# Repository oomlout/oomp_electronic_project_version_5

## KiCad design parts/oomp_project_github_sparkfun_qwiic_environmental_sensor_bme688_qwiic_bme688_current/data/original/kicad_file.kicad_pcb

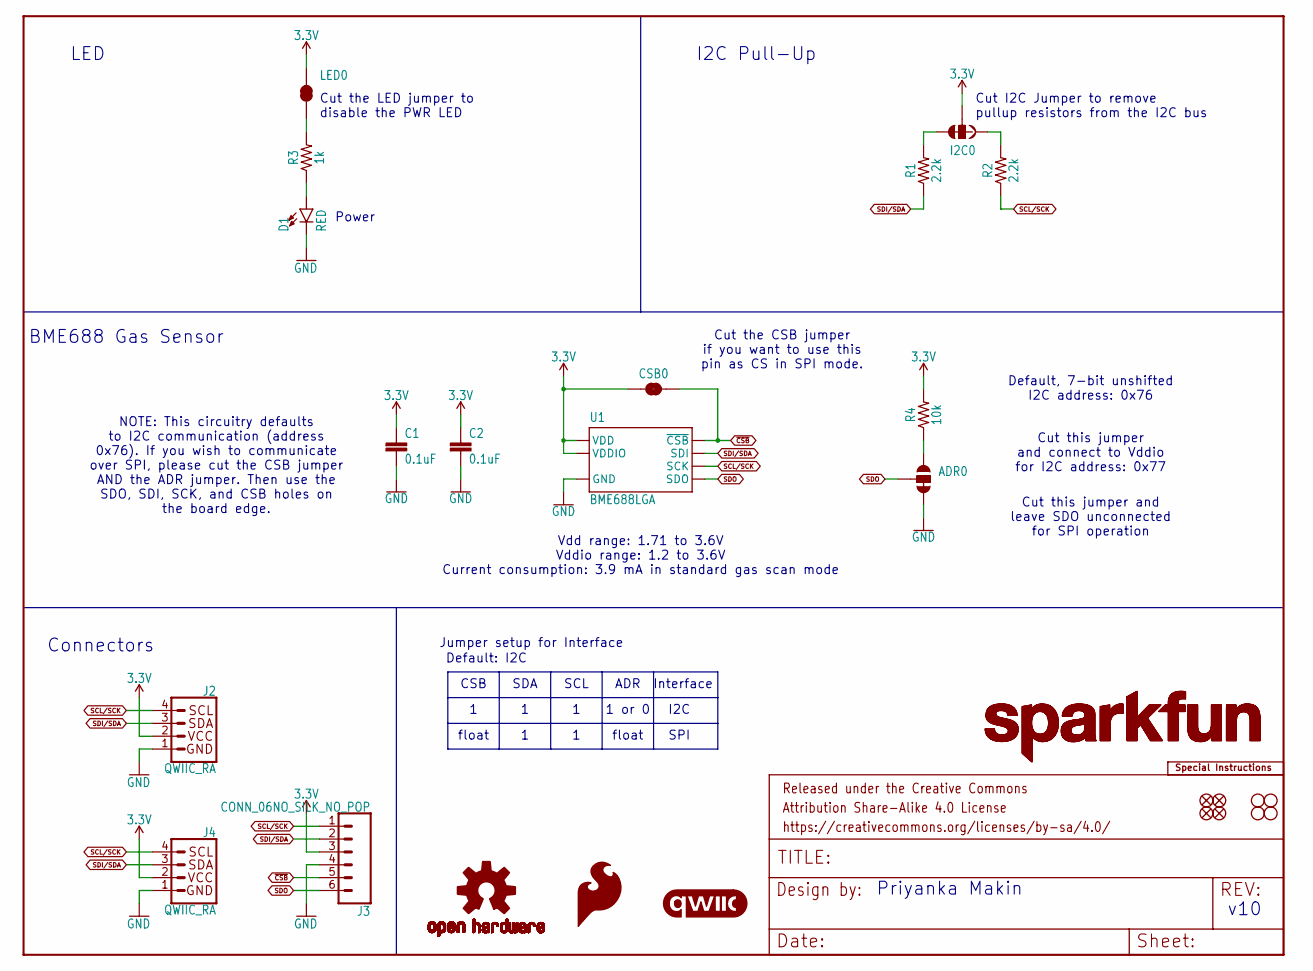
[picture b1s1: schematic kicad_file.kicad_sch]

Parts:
ADR0: JUMPER-SMT_3_1-NC_TRACE_SILK; SMT-JUMPER_3_1-NC_TRACE_SILK
C1, C2: 0.1uF; 0603
CSB0: JUMPER-SMT_2_NC_TRACE_SILK; SMT-JUMPER_2_NC_TRACE_SILK
D1: RED; LED-0603
FRAME1: FRAME-LETTER; CREATIVE_COMMONS
I2C0: JUMPER-SMT_3_2-NC_TRACE_SILK; SMT-JUMPER_3_2-NC_TRACE_SILK
J2, J4: QWIIC_RA; JST04_1MM_RA
J3: CONN_06NO_SILK_NO_POP; 1X06_NO_SILK
JP1, JP2, JP5, JP6: FIDUCIALUFIDUCIAL; FIDUCIAL-MICRO
JP3, JP4, JP7, JP8: STAND-OFF
LED0: JUMPER-SMT_2_NC_TRACE_SILK; SMT-JUMPER_2_NC_TRACE_SILK
LOGO1: SPECIAL_INSTRUCTIONS-ORDERING; ORDERING_INSTRUCTIONS
LOGO2: QWIIC_LOGO_5MM; QWIIC_5MM
LOGO3, LOGO6: SFE_LOGO_NAME.1_INCH; SFE_LOGO_NAME_.1
LOGO4: SFE_LOGO_FLAME.1_INCH; SFE_LOGO_FLAME_.1
LOGO5: OSHW-LOGOS; OSHW-LOGO-S
R1, R2: 2.2k; 0603
R3: 1k; 0603
R4: 10k; 0603
U1: BME688LGA; LGA_8PIN

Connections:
3.3V: C1.1, C2.1, CSB0.1, I2C0.2, J2.2, J3.3, J4.2, LED0.2, R4.2, U1.6 (VDDIO), U1.8 (VDD)
GND: ADR0.3, C1.2, C2.2, D1.C, J2.1, J3.4, J4.1, U1.1 (GND), U1.7 (GND)
unnamed: LED0.1, R3.2
unnamed: I2C0.3, R1.2
unnamed: D1.A, R3.1
unnamed: I2C0.1, R2.2
unnamed: ADR0.1, R4.1
SCL/SCK: J2.4, J3.1, J4.4, R2.1, U1.4 (SCK)
SDI/SDA: J2.3, J3.2, J4.3, R1.1, U1.3 (SDI)
SDO: ADR0.2, J3.6, U1.5 (SDO)
~CSB: CSB0.2, J3.5, U1.2 (~CSB)

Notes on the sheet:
Priyanka Makin
Cut the LED jumper to disable the PWR LED
Cut this jumper and connect to Vddio for I2C address: 0x77
float
LED
v10
1 or 0
NOTE: This circuitry defaults to I2C communication (address 0x76). If you wish to communicate over SPI, please cut the CSB jumper AND the ADR jumper. Then use the SDO, SDI, SCK, and CSB holes on the board edge.
Cut I2C Jumper to remove pullup resistors from the I2C bus
Default: I2C
BME688 Gas Sensor
I2C
Jumper setup for Interface
Interface
Connectors
Cut this jumper and leave SDO unconnected for SPI operation~{}
SCL
ADR
Power
SPI
SDA
Vdd range: 1.71 to 3.6V Vddio range: 1.2 to 3.6V Current consumption: 3.9 mA in standard gas scan mode
I2C Pull-Up
Default, 7-bit unshifted I2C address: 0x76
Cut the CSB jumper if you want to use this pin as CS in SPI mode.
CSB

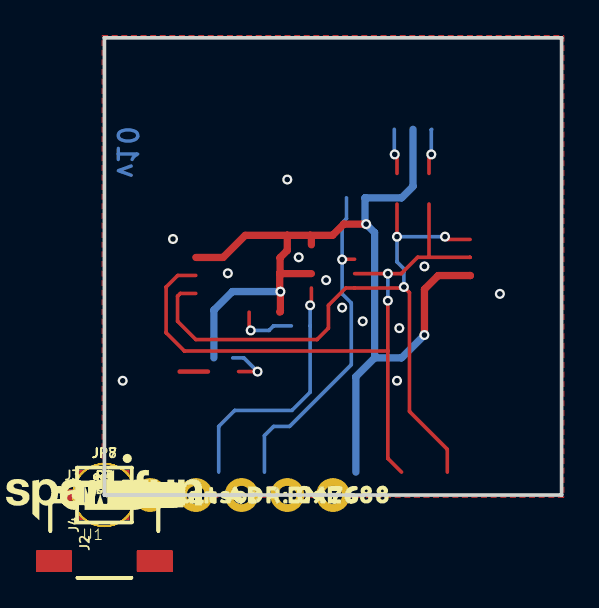
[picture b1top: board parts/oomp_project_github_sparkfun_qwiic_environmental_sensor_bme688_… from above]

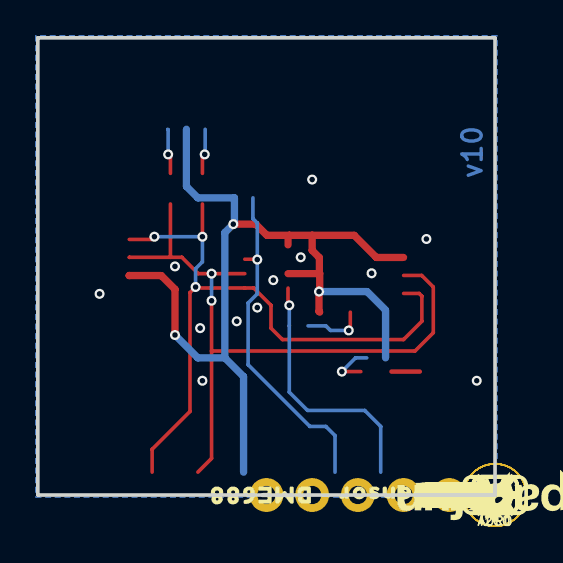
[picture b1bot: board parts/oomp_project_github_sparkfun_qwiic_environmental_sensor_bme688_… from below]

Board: 2 copper layers, 25.4 x 25.4 mm, 52 parts (22 on the bottom side), 11 nets.

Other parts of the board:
U$1, U$33: #GND#0
U$2, U$16: #SDO#0
U$3: #CSB#0
U$5: PWR0
U$6: #I2C#0
U$7, U$10: GAS_SENSOR_#_BME6880
U$8: #LED#0
U$9: 0X760
U$11: #ADR#0
U$12: DEFAULT_ADR#_0X760
U$13: 0X770
U$14, U$15: #3V3#0
U$19: #SDI#0
U$20: #SCK#0
U$21, U$22: ##CSB##0
U$35: #SDA#0
U$36: #SCL#0

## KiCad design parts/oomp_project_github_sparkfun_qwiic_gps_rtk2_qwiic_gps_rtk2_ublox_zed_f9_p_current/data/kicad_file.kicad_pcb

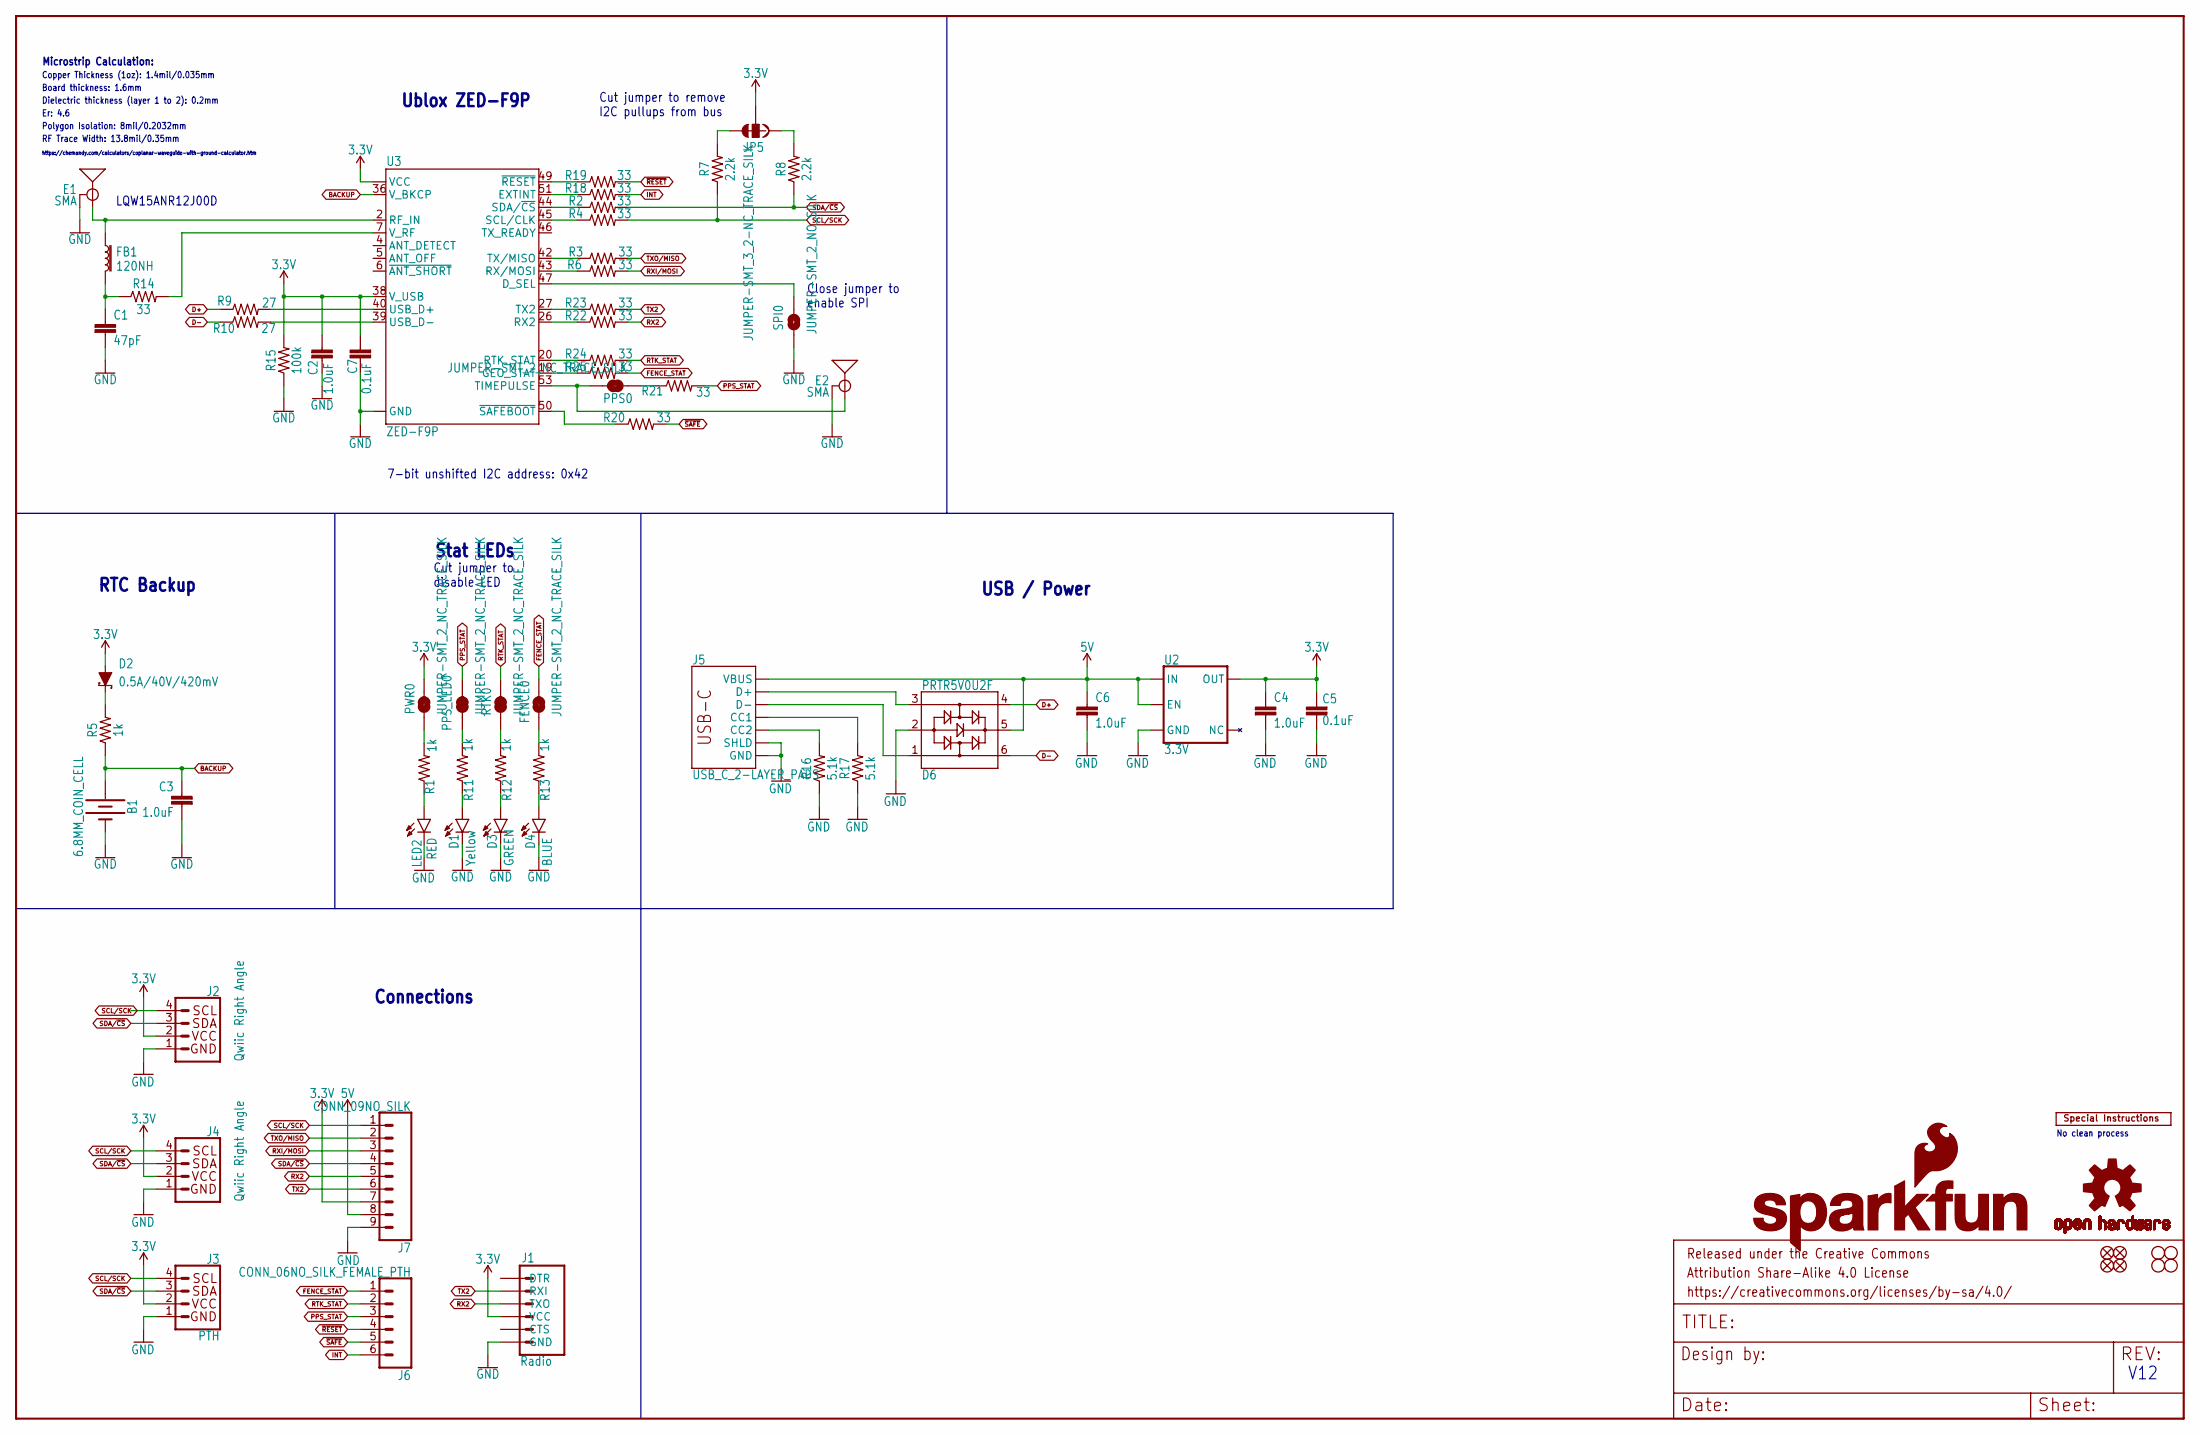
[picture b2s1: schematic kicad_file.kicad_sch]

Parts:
B1: 6.8MM_COIN_CELL; ML414H_IV01E
C1: 47pF; 0402
C2, C3, C4, C6: 1.0uF; 0603
C5, C7: 0.1uF; 0603
D1: Yellow; LED-0603
D2: 0.5A/40V/420mV; SOD-323
D3: GREEN; LED-0603
D4: BLUE; LED-0603
D6: PRTR5V0U2F; SOT886
E1, E2: SMA; SMA-EDGE
FB1: 120NH; 0402_MURATA
FENCE0: JUMPER-SMT_2_NC_TRACE_SILK; SMT-JUMPER_2_NC_TRACE_SILK
FRAME2: FRAME-LEDGER; CREATIVE_COMMONS
J1: Radio; 1X06_NO_SILK
J2, J4: Qwiic Right Angle; JST04_1MM_RA
J3: PTH; 1X04_NO_SILK
J5: USB_C_2-LAYER_PADS; USB-C-16P-2LAYER-PADS
J6: CONN_06NO_SILK_FEMALE_PTH; 1X06_NO_SILK
J7: CONN_09NO_SILK; 1X09_NO_SILK
JP5: JUMPER-SMT_3_2-NC_TRACE_SILK; SMT-JUMPER_3_2-NC_TRACE_SILK
JP21, JP61, JP71, JP81: FIDUCIALUFIDUCIAL; MICRO-FIDUCIAL
JP31, JP41, JP91, JP101: STAND-OFF
LED2: RED; LED-0603
LOGO1: OSHW-LOGOMINI; OSHW-LOGO-MINI
LOGO2: SFE_LOGO_NAME_FLAME.1_INCH; SFE_LOGO_NAME_FLAME_.1
PPS0: JUMPER-SMT_2_NC_TRACE_SILK; SMT-JUMPER_2_NC_TRACE_SILK
PPS_LED0: JUMPER-SMT_2_NC_TRACE_SILK; SMT-JUMPER_2_NC_TRACE_SILK
PWR0: JUMPER-SMT_2_NC_TRACE_SILK; SMT-JUMPER_2_NC_TRACE_SILK
R1, R5, R11, R12, R13: 1k; 0603
R2, R3, R4, R6, R14, R18, R19, R20, R21, R22, R23, R24, R25: 33; 0603
R7, R8: 2.2k; 0603
R9, R10: 27; 0603
R15: 100k; 0603
R16, R17: 5.1k; 0603
RTK0: JUMPER-SMT_2_NC_TRACE_SILK; SMT-JUMPER_2_NC_TRACE_SILK
SPI0: JUMPER-SMT_2_NO_SILK; SMT-JUMPER_2_NO_SILK
U2: 3.3V; SOT23-5
U3: ZED-F9P
U$2: SPECIAL_INSTRUCTIONS-ORDERING; ORDERING_INSTRUCTIONS

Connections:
3.3V: C2.1, C4.1, C5.2, C7.2, D2.A, J1.4 (VCC), J2.2, J3.2 (VCC), J4.2, J7.7, JP5.2, PWR0.2, R15.2, U2.5 (OUT), U3.33 (VCC), U3.34 (VCC), U3.38 (V_USB)
5V: C6.1, D6.5, J5.VBUS1 (VBUS), J5.VBUS2 (VBUS), J7.8, U2.1 (IN), U2.3 (EN)
ANT_VCC: C1.1, FB1.P2 (2), R14.1
BACKUP: B1.+, C3.1, R5.1, U3.36 (V_BKCP)
CC1: J5.A5 (CC1), R17.2
CC2: J5.B5 (CC2), R16.2
D+: D6.4, R9.1
D-: D6.6, R10.1
D_SEL: SPI0.2, U3.47 (D_SEL)
FENCE_STAT: FENCE0.2, J6.1, R25.2
GND: B1.-, C1.2, C2.2, C3.2, C4.2, C5.1, C6.2, C7.1, D1.C, D3.C, D4.C, D6.2, E1.GND@0 (GND), E1.GND@1 (GND), E1.GND@2 (GND), E1.GND@3 (GND), E2.GND@0 (GND), E2.GND@1 (GND), E2.GND@2 (GND), E2.GND@3 (GND), J1.6 (GND), J2.1, J3.1 (GND), J4.1, J5.GND, J5.GND2 (GND), J5.SHLD1 (SHLD), J5.SHLD2 (SHLD), J5.SHLD3 (SHLD), J5.SHLD4 (SHLD), J7.9, LED2.C, R15.1, R16.1, R17.1, SPI0.1, U2.2 (GND), U3.1 (GND), U3.3 (GND), U3.12 (GND), U3.14 (GND), U3.32 (GND), U3.37 (GND), U3.41 (GND), U3.48 (GND), U3.55 (GND), U3.56 (GND), U3.57 (GND), U3.58 (GND), U3.59 (GND), U3.60 (GND), U3.61 (GND), U3.62 (GND), U3.63 (GND), U3.64 (GND), U3.65 (GND), U3.66 (GND), U3.67 (GND), U3.68 (GND), U3.69 (GND), U3.70 (GND), U3.71 (GND), U3.72 (GND), U3.73 (GND), U3.74 (GND), U3.75 (GND), U3.76 (GND), U3.77 (GND), U3.78 (GND), U3.79 (GND), U3.80 (GND), U3.81 (GND), U3.82 (GND), U3.83 (GND), U3.84 (GND), U3.85 (GND), U3.86 (GND), U3.87 (GND), U3.88 (GND), U3.89 (GND), U3.90 (GND), U3.91 (GND), U3.92 (GND), U3.93 (GND), U3.94 (GND), U3.95 (GND), U3.96 (GND), U3.97 (GND), U3.98 (GND), U3.99 (GND), U3.100 (GND), U3.101 (GND), U3.102 (GND)
GPS_ANT1: E1.SIG (SIGNAL), FB1.P1 (1), U3.2 (RF_IN)
INT: J6.6, R18.2
unnamed: D3.A, R12.1
unnamed: D1.A, R11.1
unnamed: R12.2, RTK0.1
unnamed: PPS_LED0.1, R11.2
unnamed: JP5.1, R8.2
unnamed: D2.C, R5.2
unnamed: D4.A, R13.1
unnamed: JP5.3, R7.2
unnamed: FENCE0.1, R13.2
unnamed: LED2.A, R1.1
unnamed: R9.2, U3.40 (USB_D+)
unnamed: R10.2, U3.39 (USB_D-)
unnamed: R14.2, U3.7 (V_RF)
unnamed: R22.1, U3.26 (RX2)
unnamed: R18.1, U3.51 (EXTINT)
unnamed: R19.1, U3.49 (~RESET)
unnamed: PWR0.1, R1.2
unnamed: R20.1, U3.50 (~SAFEBOOT)
unnamed: R24.1, U3.20 (RTK_STAT)
unnamed: R25.1, U3.19 (GEO_STAT)
unnamed: PPS0.1, R21.1
PPS: E2.SIG (SIGNAL), PPS0.2, U3.53 (TIMEPULSE)
PPS_STAT: J6.3, PPS_LED0.2, R21.2
RTK_STAT: J6.2, R24.2, RTK0.2
RX2: J1.3 (TXO), J7.5, R22.2
RXI/MOSI: J7.3, R6.2
RXLV: R6.1, U3.43 (RX/MOSI)
SCL/SCK: J2.4, J3.4 (SCL), J4.4, J7.1, R4.2, R7.1
SCL_LV: R4.1, U3.45 (SCL/CLK)
SDA/~CS: J2.3, J3.3 (SDA), J4.3, J7.4, R2.2, R8.1
SDA_LV: R2.1, U3.44 (SDA/~CS)
TX2: J1.2 (RXI), J7.6, R23.2
TX2_P: R23.1, U3.27 (TX2)
TXLV: R3.1, U3.42 (TX/MISO)
TXO/MISO: J7.2, R3.2
UNP_D+: D6.3, J5.A6 (D+), J5.B6 (D+)
UNP_D-: D6.1, J5.A7 (D-), J5.B7 (D-)
~RESET: J6.4, R19.2
~SAFE: J6.5, R20.2

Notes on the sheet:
V12
RTC Backup
Dielectric thickness (layer 1 to 2): 0.2mm
https://chemandy.com/calculators/coplanar-waveguide-with-ground-calculator.htm
Er: 4.6
LQW15ANR12J00D
Polygon Isolation: 8mil/0.2032mm
Ublox ZED-F9P
Connections
7-bit unshifted I2C address: 0x42
Board thickness: 1.6mm
Cut jumper to remove I2C pullups from bus
RF Trace Width: 13.8mil/0.35mm
No clean process
Stat LEDs
Close jumper to enable SPI
USB / Power
Cut jumper to disable LED
Copper Thickness (1oz): 1.4mil/0.035mm
Microstrip Calculation:

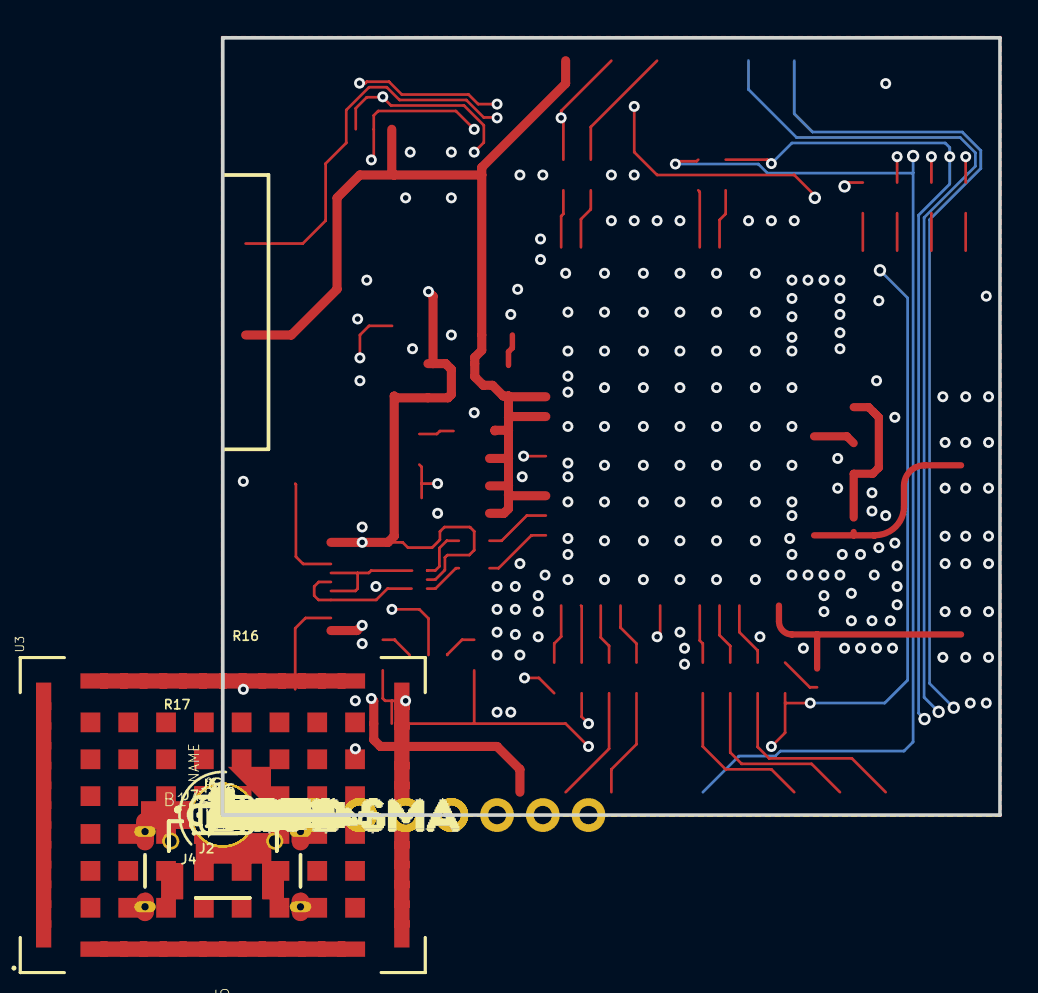
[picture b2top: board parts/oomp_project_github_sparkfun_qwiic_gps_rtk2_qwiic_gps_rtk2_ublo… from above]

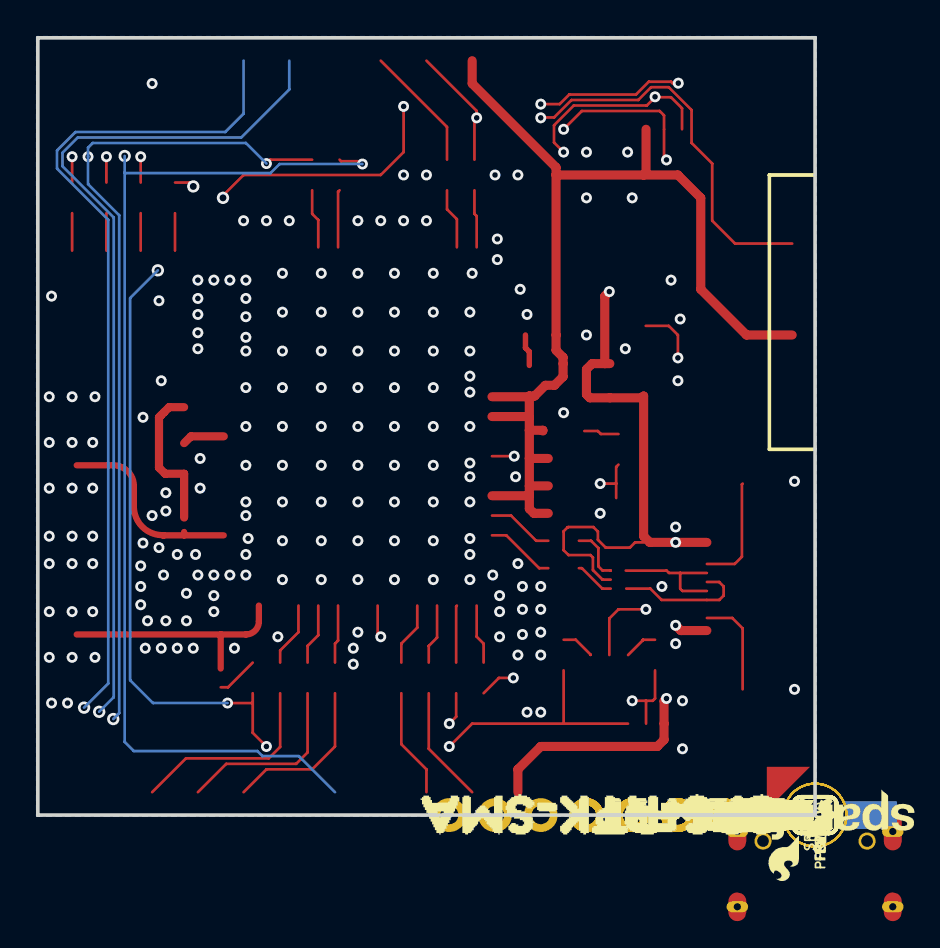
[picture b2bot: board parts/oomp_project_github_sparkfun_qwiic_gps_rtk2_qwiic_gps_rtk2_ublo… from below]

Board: 4 copper layers, 43.2 x 43.2 mm, 143 parts (44 on the bottom side), 52 nets.

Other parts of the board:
U$1, U$4: SDA-[)
U$3, U$5: SCL-[)
U$6, U$7, U$60, U$61, U$66, U$67: 3V3-04
U$8, U$9, U$62, U$63: GND-04
U$10: I_SUPER2_C-()-03
U$11, U$54: FENCE2
U$12, U$18: PWR-()-03
U$13, U$28, U$29, U$32: RTK1
U$14, U$17: FENCE0
U$15, U$16: INT8
U$19, U$20: 5V
U$21, U$56, U$58: RX20
U$22: U#BLOX3
U$23, U$24: CS#-_]
U$25, U$52, U$72: PPS0
U$26, U$31: RX#MOSI3
U$27: DSEL0
U$30: QWIIC_4MM
U$33: SFE_LOGO_FLAME_.1
U$34, U$37: TX#MISO1
U$35, U$36: #RST3
U$38, U$41: SCK-(]-04
U$39, U$40: #SAFE1
U$42: RX22
U$43, U$44: PPS5
U$45, U$68: GND3
U$47, U$74: PPS1
U$48, U$70: RTCM5
U$49: ZED#F9P6
U$50, U$55, U$57: TX21
U$51: TX23
U$53, U$69: CORRECTION0
U$59: GPS0
U$65: ACTIVE_L1#L21
U$71, U$75: ANTENNA2
U$73: RTK#SMA4
U$76: GPS#RTK#SMA5

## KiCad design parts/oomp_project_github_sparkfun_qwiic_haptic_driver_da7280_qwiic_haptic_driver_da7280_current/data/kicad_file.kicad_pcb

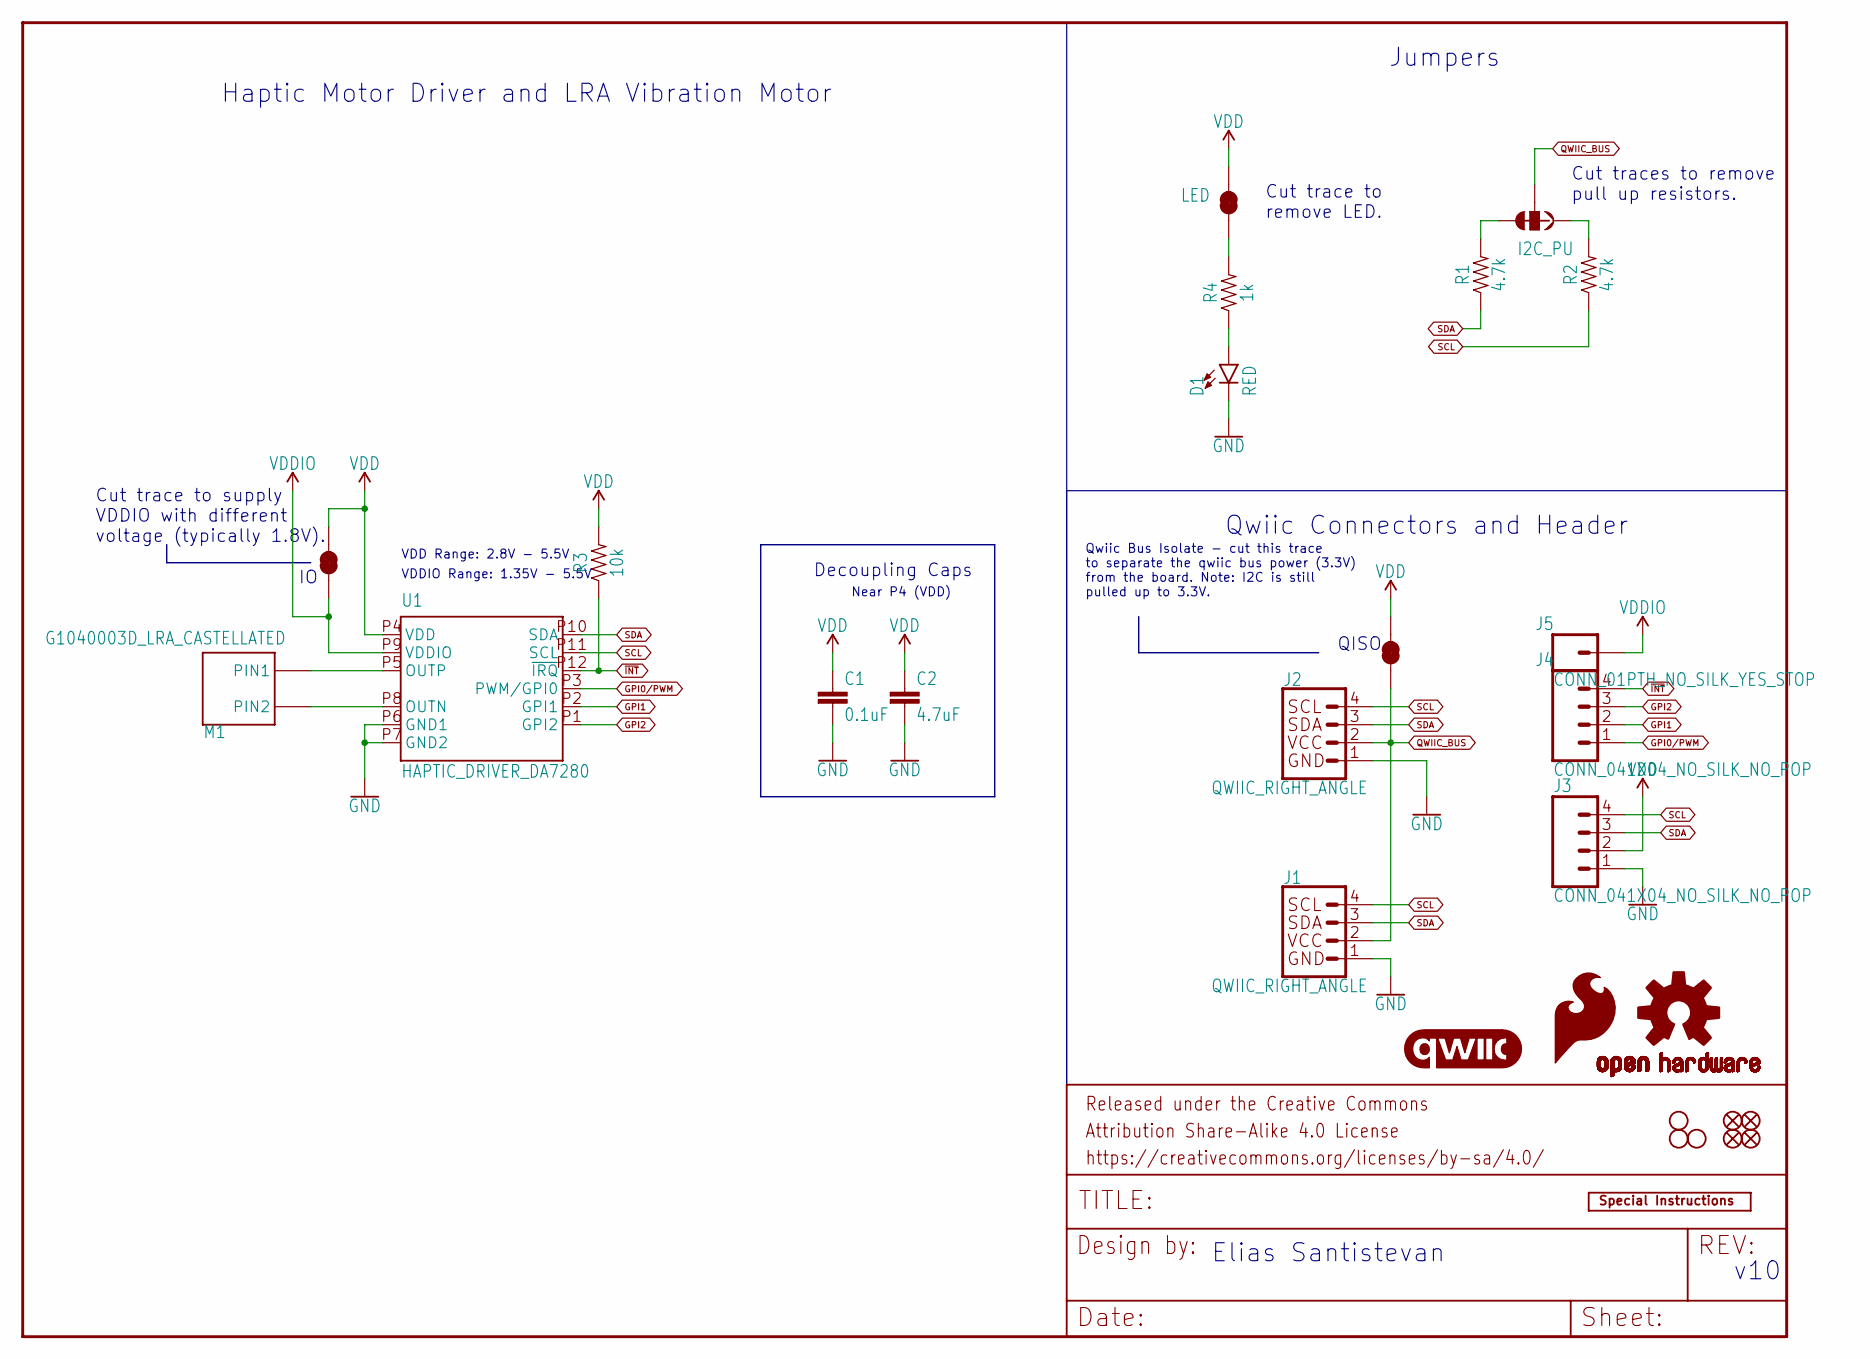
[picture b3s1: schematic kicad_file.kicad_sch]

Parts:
C1: 0.1uF; 0603
C2: 4.7uF; 0603
D1: RED; LED-0603
FD1, FD2, FD3, FD4: FIDUCIALUFIDUCIAL; FIDUCIAL-MICRO
FRAME1: FRAME-LETTER; CREATIVE_COMMONS
H1, H2, H4: STAND-OFFTIGHT; STAND-OFF-TIGHT
J1, J2: QWIIC_RIGHT_ANGLE; JST04_1MM_RA
J3, J4: CONN_041X04_NO_SILK_NO_POP; 1X04_NO_SILK
J5: CONN_01PTH_NO_SILK_YES_STOP; 1X01_NO_SILK
JP1, JP2, JP4: LED; SMT-JUMPER_2_NC_TRACE_SILK
JP3: I2C_PU; SMT-JUMPER_3_2-NC_TRACE_SILK
LOGO1: SPECIAL_INSTRUCTIONS-ORDERING; ORDERING_INSTRUCTIONS
LOGO2: OSHW-LOGOS; OSHW-LOGO-S
LOGO4: SFE_LOGO_FLAME.1_INCH; SFE_LOGO_FLAME_.1
M1: G1040003D_LRA_CASTELLATED; COIN_VIBRATION_MOTOR_CASTEL
R1, R2: 4.7k; 0603
R3: 10k; 0603
R4: 1k; 0603
U1: HAPTIC_DRIVER_DA7280; QFN_DA7280
U$1: QWIIC_LOGO_3MM; QWIIC_3MM

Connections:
GND: C1.2, C2.2, D1.C, J1.1, J2.1, J3.1, U1.P6 (GND1), U1.P7 (GND2)
GPI0/PWM: J4.1, U1.P3 (PWM/GPI0)
GPI1: J4.2, U1.P2 (GPI1)
GPI2: J4.3, U1.P1 (GPI2)
unnamed: D1.A, R4.1
unnamed: JP1.1, R4.2
unnamed: JP3.3, R1.2
unnamed: JP3.1, R2.2
unnamed: M1.P$1 (PIN1), U1.P5 (OUTP)
unnamed: M1.P$2 (PIN2), U1.P8 (OUTN)
QWIIC_BUS: J1.2, J2.2, JP3.2, JP4.1
SCL: J1.4, J2.4, J3.4, R2.1, U1.P11 (SCL)
SDA: J1.3, J2.3, J3.3, R1.1, U1.P10 (SDA)
VDD: C1.1, C2.1, J3.2, JP1.2, JP2.2, JP4.2, R3.2, U1.P4 (VDD)
VDDIO: J5.1, JP2.1, U1.P9 (VDDIO)
~INT: J4.4, R3.1, U1.P12 (~IRQ)

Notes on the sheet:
v10
Qwiic Connectors and Header
Cut trace to supply VDDIO with different voltage (typically 1.8V).
Haptic Motor Driver and LRA Vibration Motor
VDDIO Range: 1.35V - 5.5V
Jumpers
Near P4 (VDD)
Elias Santistevan
QISO
Cut trace to remove LED.
Decoupling Caps
Qwiic Bus Isolate - cut this trace to separate the qwiic bus power (3.3V) from the board. Note: I2C is still pulled up to 3.3V.
VDD Range: 2.8V - 5.5V
Cut traces to remove pull up resistors.

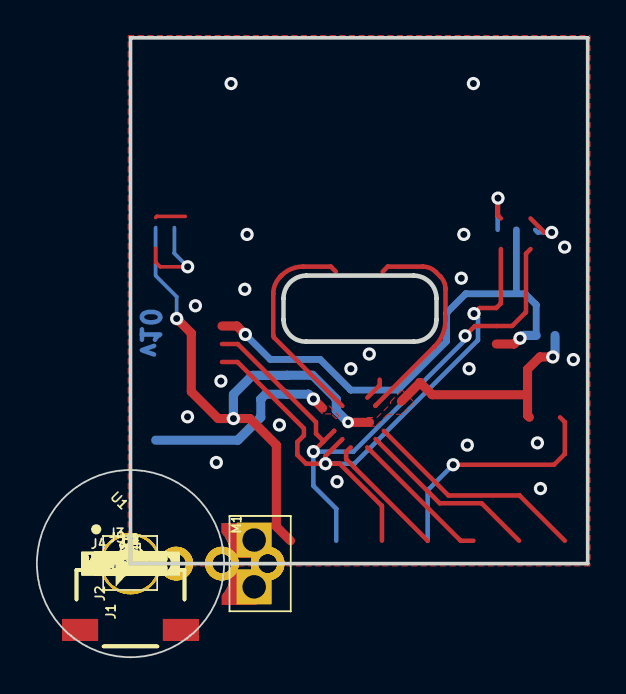
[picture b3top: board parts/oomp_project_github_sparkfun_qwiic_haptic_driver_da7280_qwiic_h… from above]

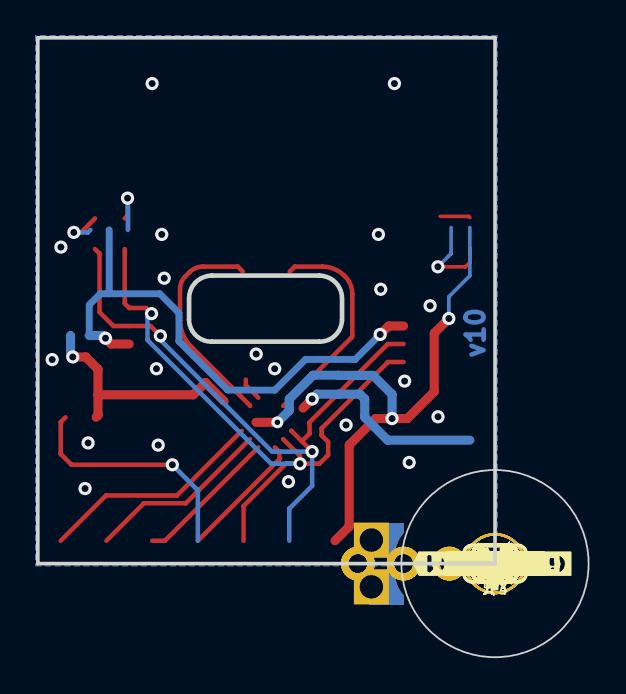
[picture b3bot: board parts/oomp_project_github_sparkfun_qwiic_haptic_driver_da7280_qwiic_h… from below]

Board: 2 copper layers, 30.6 x 34.4 mm, 58 parts (25 on the bottom side), 16 nets.

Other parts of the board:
U$2: #3V3#1
U$3, U$18: #GND#0
U$4: #GPI0#6
U$5: #GPI1#6
U$6: #GPI2#6
U$7: #VDD#4
U$8: #SDA#4
U$9: HAPTIC6
U$10: MOTOR7
U$11: DRIVER8
U$12: #GPI0#PWM#2
U$13: #GPI1#2
U$14: #GPI2#2
U$15, U$25: #VDDIO#5
U$16: #SDA#0
U$19: #SCL#5
U$20: PWR72810
U$21: #SCL#1
U$23: #I2C#4
U$24: #LED#4
U$26: SFE_LOGO_FLAME_.1
U$27: ##INT##3
U$28: ##INT##6
U$29: DA72809
U$30: #IO#6
U$31: #QISO#0

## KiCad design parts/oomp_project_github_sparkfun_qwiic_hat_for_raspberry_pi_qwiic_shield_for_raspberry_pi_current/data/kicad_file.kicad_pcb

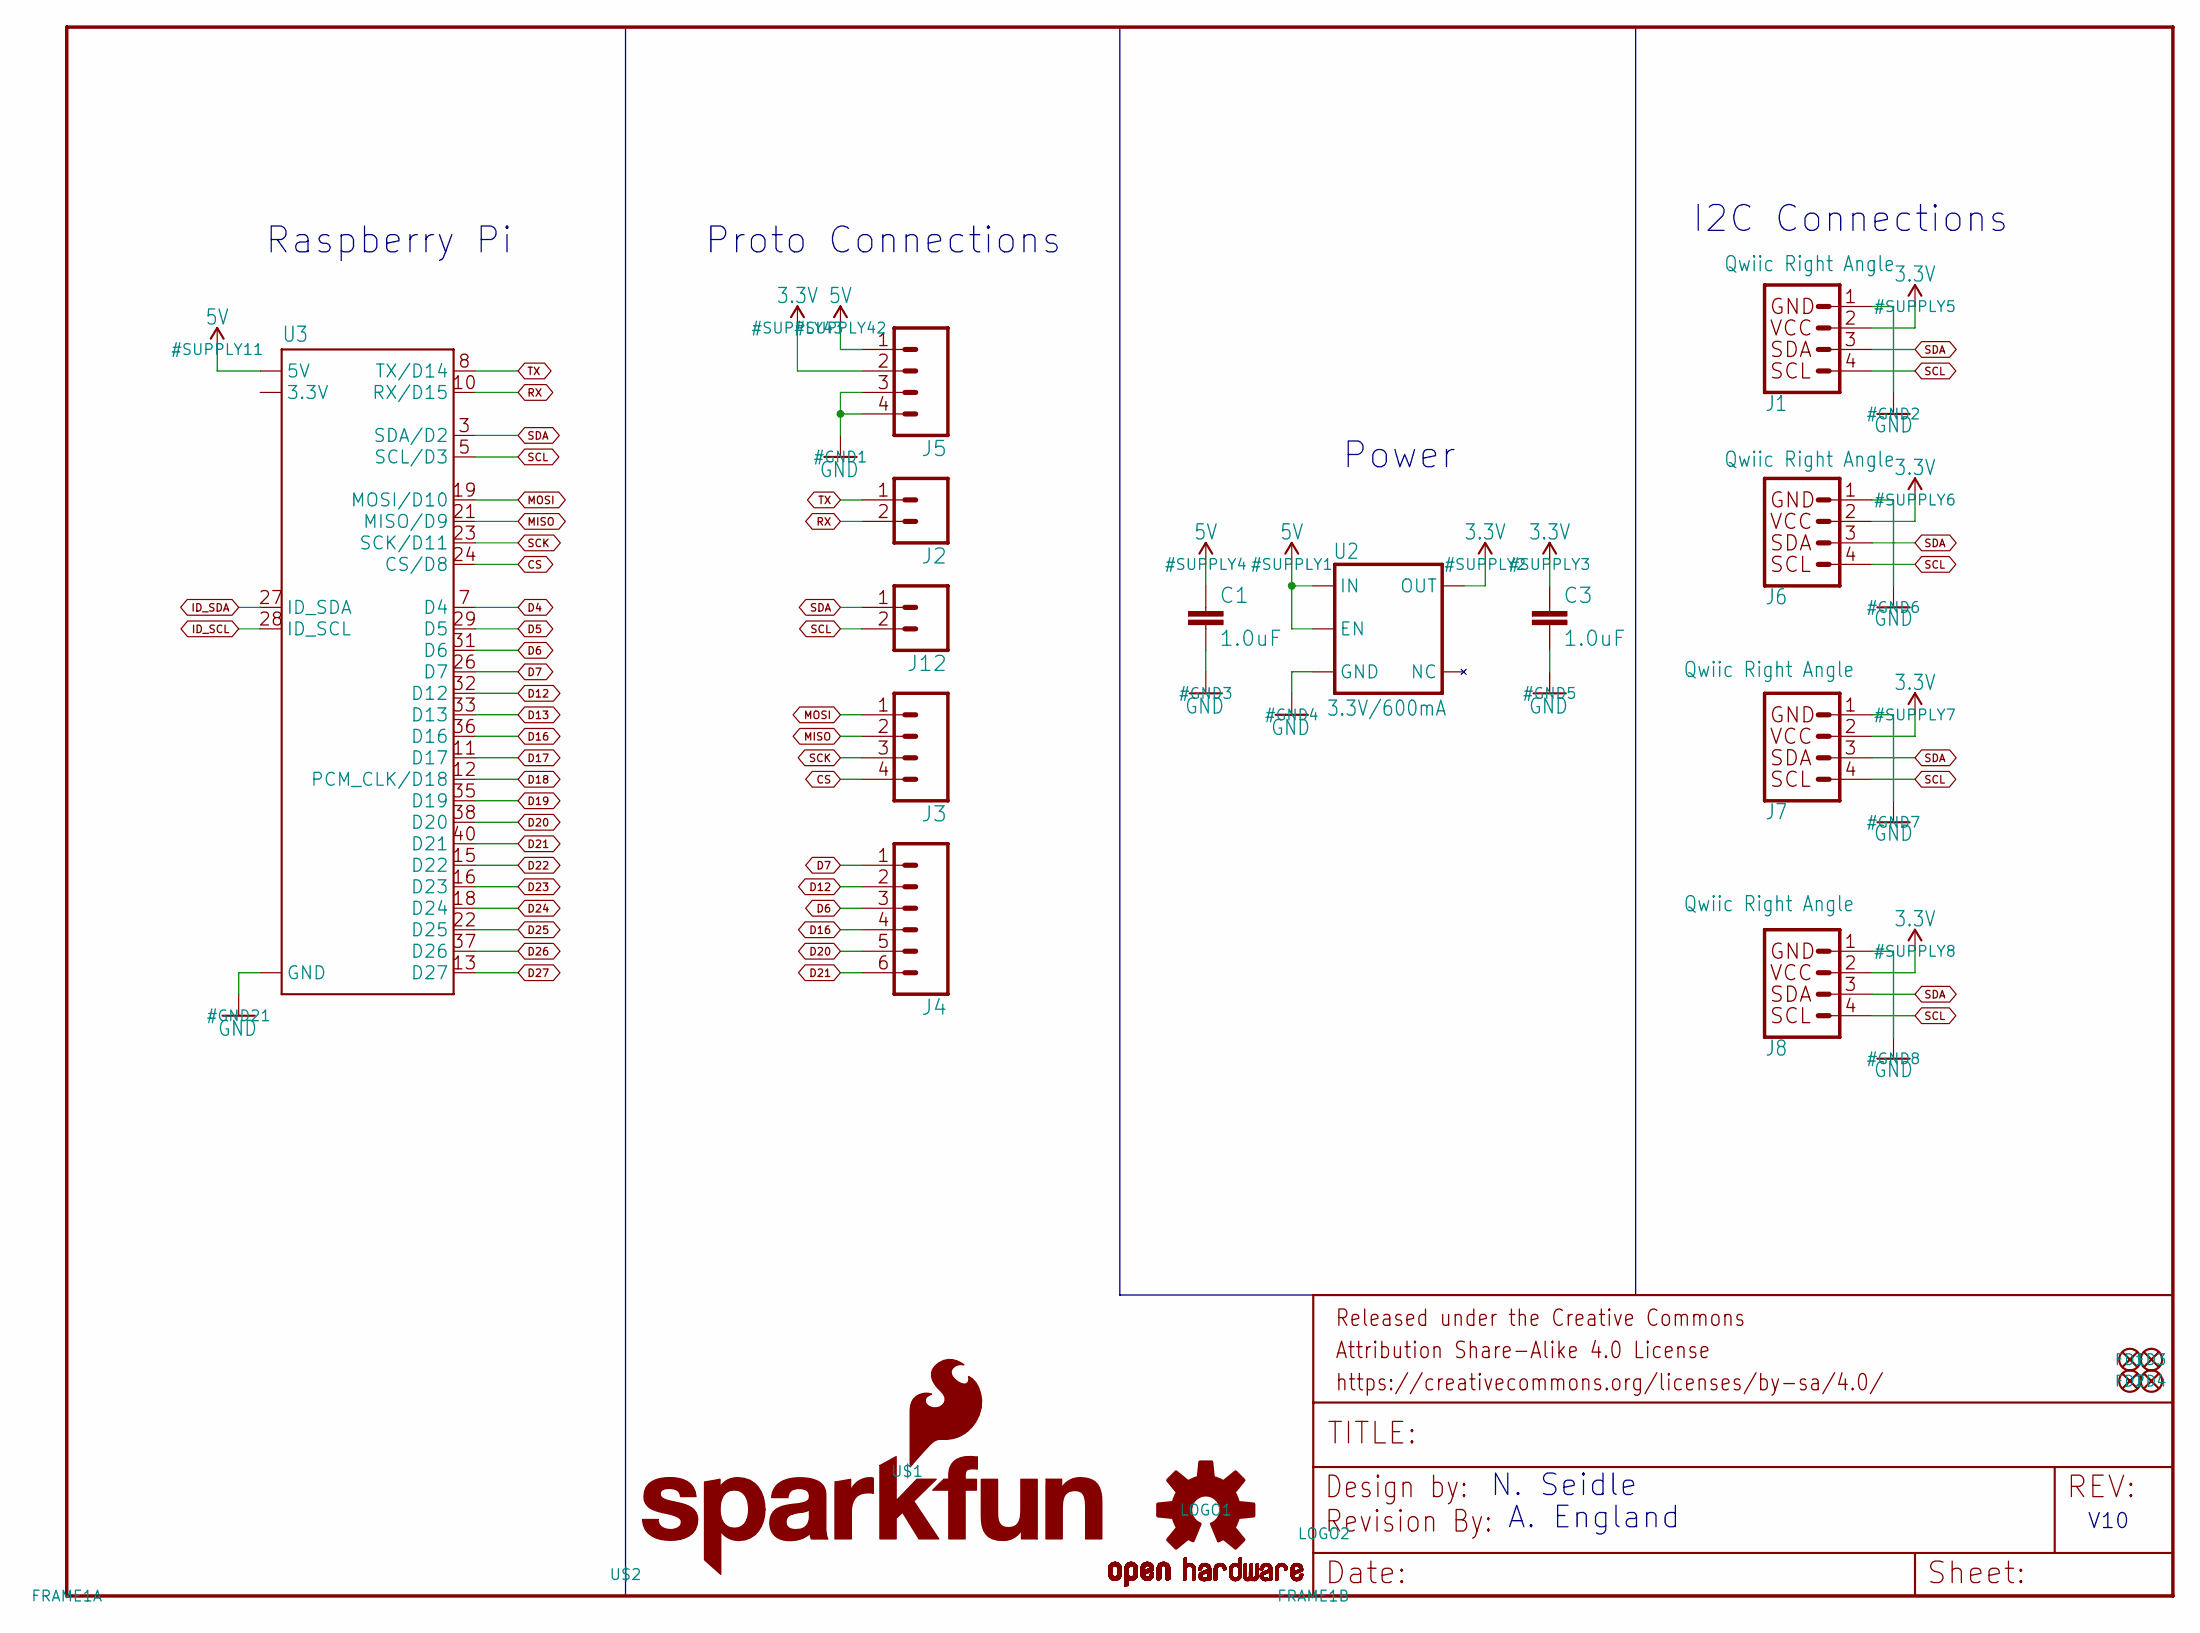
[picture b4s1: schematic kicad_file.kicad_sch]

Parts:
C1, C3: 1.0uF; 0603
FD1, FD2, FD3, FD4: FIDUCIAL1X2; FIDUCIAL-1X2
FRAME1: FRAME-LETTER; CREATIVE_COMMONS
J1, J6, J7, J8: Qwiic Right Angle; 1X04_1MM_RA
J2, J12: CONN_021X02_NO_SILK; 1X02_NO_SILK
J3, J5: CONN_041X04_NO_SILK; 1X04_NO_SILK
J4: CONN_06NO_SILK_FEMALE_PTH; 1X06_NO_SILK
LOGO1: OSHW-LOGOMINI; OSHW-LOGO-MINI
LOGO2: REVISION
U2: 3.3V/600mA; SOT23-5
U3: RASPBERRY_PI_40BTM-NOHOLES; RASPBERRY_PI_SHIELD_BOTTOM_ENTRY_NOHOLES
U$1: SFE_LOGO_FLAME.1_INCH; SFE_LOGO_FLAME_.1
U$2: SFE_LOGO_NAME.1_INCH; SFE_LOGO_NAME_.1

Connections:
3.3V: C3.1, J1.2, J5.2, J6.2, J7.2, J8.2, U2.5 (OUT)
5V: C1.1, J5.1, U2.1 (IN), U2.3 (EN), U3.2 (5V), U3.4 (5V)
CS: J3.4, U3.24 (CS/D8)
D4: U3.7 (D4)
D5: U3.29 (D5)
D6: J4.3, U3.31 (D6)
D7: J4.1, U3.26 (D7)
D12: J4.2, U3.32 (D12)
D13: U3.33 (D13)
D16: J4.4, U3.36 (D16)
D17: U3.11 (D17)
D18: U3.12 (PCM_CLK/D18)
D19: U3.35 (D19)
D20: J4.5, U3.38 (D20)
D21: J4.6, U3.40 (D21)
D22: U3.15 (D22)
D23: U3.16 (D23)
D24: U3.18 (D24)
D25: U3.22 (D25)
D26: U3.37 (D26)
D27: U3.13 (D27)
GND: C1.2, C3.2, J1.1, J5.3, J5.4, J6.1, J7.1, J8.1, U2.2 (GND), U3.6 (GND), U3.9 (GND), U3.14 (GND), U3.20 (GND), U3.25 (GND), U3.30 (GND), U3.34 (GND), U3.39 (GND)
ID_SCL: U3.28 (ID_SCL)
ID_SDA: U3.27 (ID_SDA)
MISO: J3.2, U3.21 (MISO/D9)
MOSI: J3.1, U3.19 (MOSI/D10)
RX: J2.2, U3.10 (RX/D15)
SCK: J3.3, U3.23 (SCK/D11)
SCL: J1.4, J6.4, J7.4, J8.4, J12.2, U3.5 (SCL/D3)
SDA: J1.3, J6.3, J7.3, J8.3, J12.1, U3.3 (SDA/D2)
TX: J2.1, U3.8 (TX/D14)

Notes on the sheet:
Raspberry Pi
Power
A. England
Proto Connections
V10
I2C Connections
N. Seidle

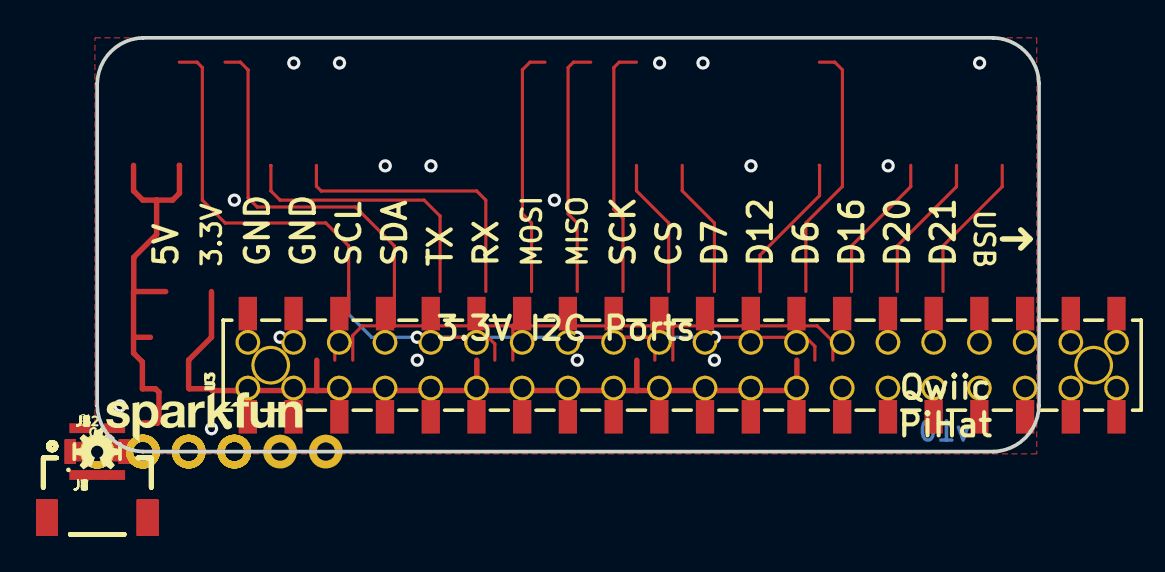
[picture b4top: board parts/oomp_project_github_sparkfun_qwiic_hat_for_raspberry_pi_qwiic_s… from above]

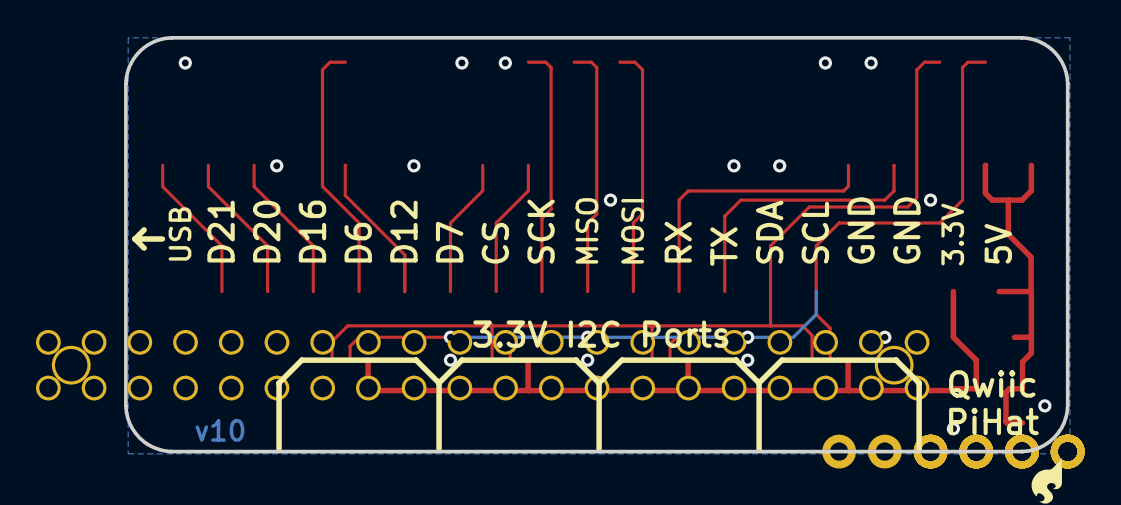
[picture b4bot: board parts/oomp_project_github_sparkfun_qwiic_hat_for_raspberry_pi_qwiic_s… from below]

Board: 2 copper layers, 52.3 x 23.0 mm, 22 parts (3 on the bottom side), 17 nets.

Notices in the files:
parts/oomp_project_github_sparkfun_qwiic_environmental_sensor_bme688_qwiic_bme688_current/data/original/kicad_file.kicad_sch:
Released under the Creative Commons
https://creativecommons.org/licenses/by-sa/4.0
parts and their libraries:
Released under the Creative Commons Attribution Share-Alike 4.0 License
